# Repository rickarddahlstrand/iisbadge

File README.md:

# iisbadge
The IIS Internetdagarna Badge project.

Here is a collection of the Eagle source files for the IIS Internetdagarna badge projekt.

All the parts can be ordered from Seeedstudio and their excellent OPL:
http://www.seeedstudio.com/depot/OPLopen-parts-library-catalog-c-136_138/?ref=crumb

* 1 x DIP Toggle Switch;6P-2.54-L9.0*W3.5*H3.2mm(311030004)
* 2 x DIP LED Vaporous-Red-Red(304090059)
* 1 x Lithium-ion Battery 3V-40mAh(313010013)
* 1 x DIP Battery Cell Holder;(320170002)
* 1 x Folding Clasps(323050000

Needed for the geekprt:
* 1 x DIP Black Male Header VERT;(320020010)
* 2 x DIP RES 100R-5%-1/4W(301020017)

<br>
<a href="https://github.com/rickarddahlstrand/iisbadge/raw/master/intdagarnapulseheart.ino">Code example for this here!</a>

License: CC BY-NC-SA 3.0

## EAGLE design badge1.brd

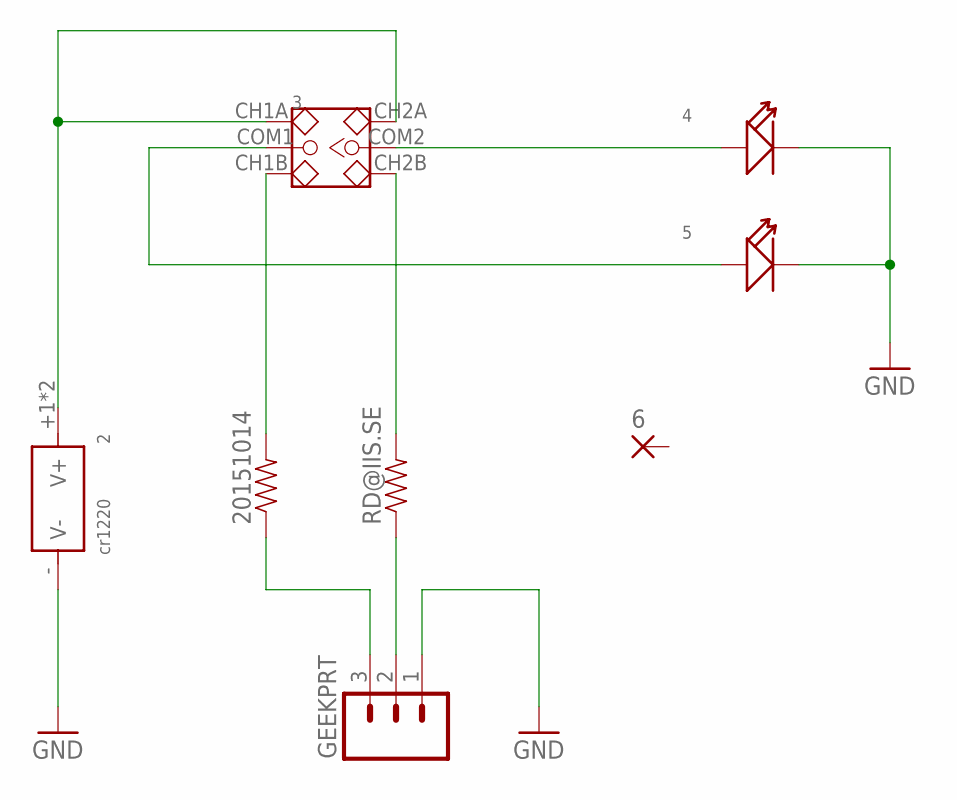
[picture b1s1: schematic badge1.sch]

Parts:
2: cr1220; BAT2P-13.5-CR1220
3: DIP-TOGGLE-SWITCH-2CH-(2X3P-2.54-90D)'90D'; SW6-2.54-9.0X3.5X3.2MM-90D
4, 5: LED'5MM'; LED2-2.54-D5.0MM
6: 3,81/1,4
20151014: RESISTORPTH-1/4W; AXIAL-0.4
GEEKPRT: M03LOCK; 1X03_LOCK
RD@IIS.SE: RESISTORPTH-1/4W; AXIAL-0.4

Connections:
GND: 2.- (V-), 4.-, 5.-, GEEKPRT.1
unnamed: 3.COM2, 4.+
unnamed: 3.COM1, 5.+
unnamed: 2.+1 (V+), 2.+2 (V+), 3.CH1A, 3.CH2A
unnamed: GEEKPRT.2, RD@IIS.SE.P$1 (1)
unnamed: 3.CH1B, 20151014.P$2 (2)
unnamed: 3.CH2B, RD@IIS.SE.P$2 (2)
unnamed: 20151014.P$1 (1), GEEKPRT.3

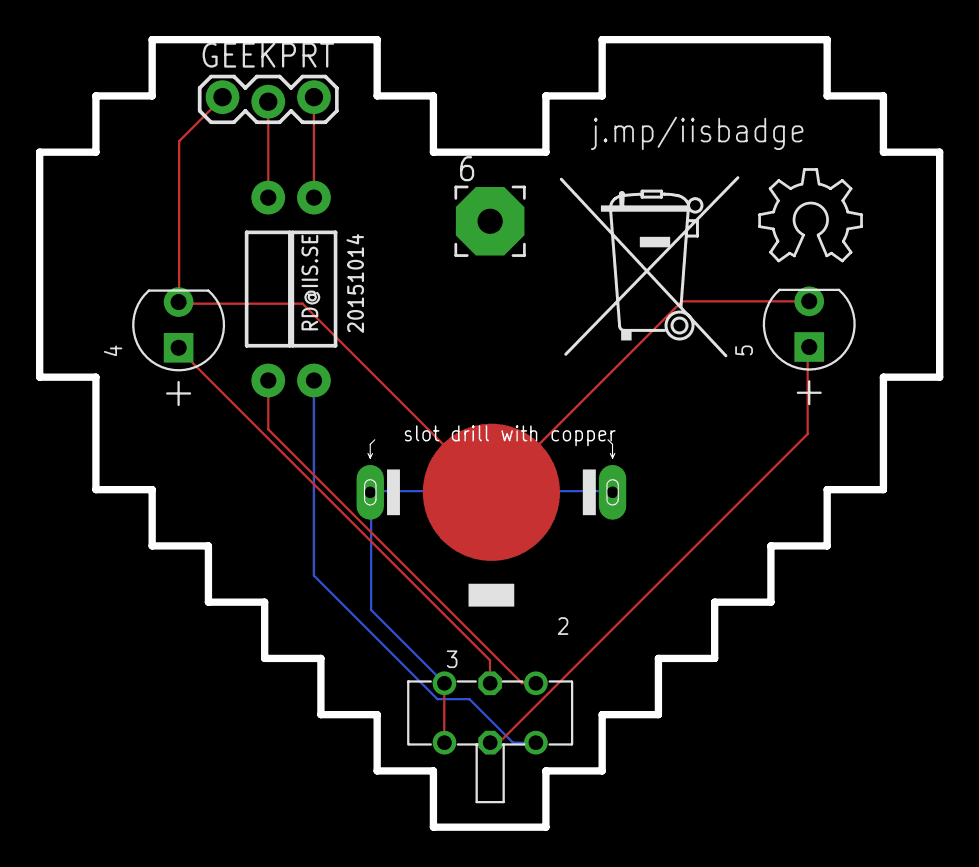
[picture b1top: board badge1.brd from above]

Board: 2 copper layers, 50.0 x 43.8 mm, 10 parts (0 on the bottom side), 8 nets.

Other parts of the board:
U$1: OSHW_6X200_NOTEXT
U$3: MUELLTONNE_10.00

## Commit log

2015-09-25 First commit
    ..
2015-09-25 Second rev send to dirtypcb
2015-10-14 Rev 3 sent to Cogra
2015-11-04 Added instructions..
2015-11-05 Instructions in Swedish.
2015-11-26 Added movie for geekprt.
2015-11-26 Update README.md
    Added geekprt movie.
2015-11-26 Gif-version of the movie.
2015-11-26 Added code for pulsating heart
2015-11-26 Update README.md
    Added gif to show pulsating heart.

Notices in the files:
parts and their libraries:
SparkFun-Connectors: Licensing: Creative Commons ShareAlike 4.0 International - https://creativecommons.org/licenses/by-sa/4.0
